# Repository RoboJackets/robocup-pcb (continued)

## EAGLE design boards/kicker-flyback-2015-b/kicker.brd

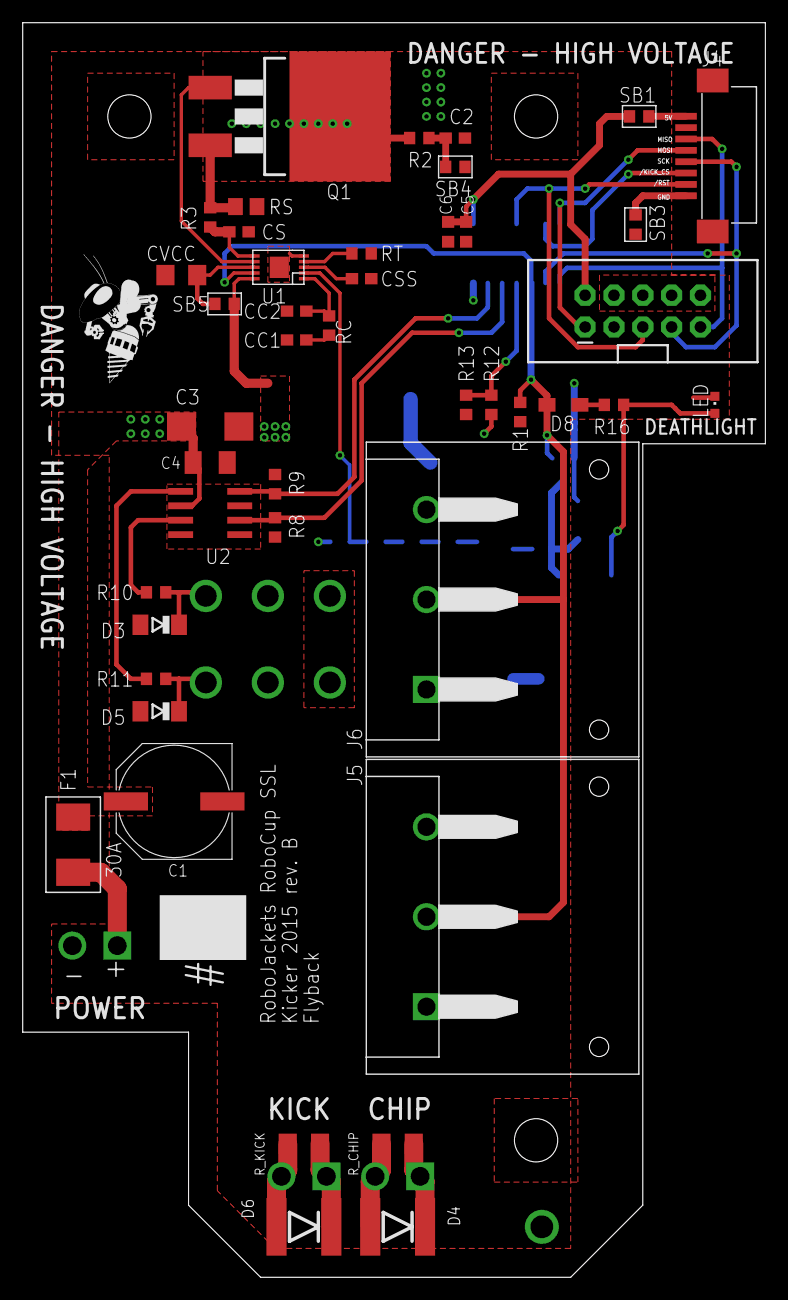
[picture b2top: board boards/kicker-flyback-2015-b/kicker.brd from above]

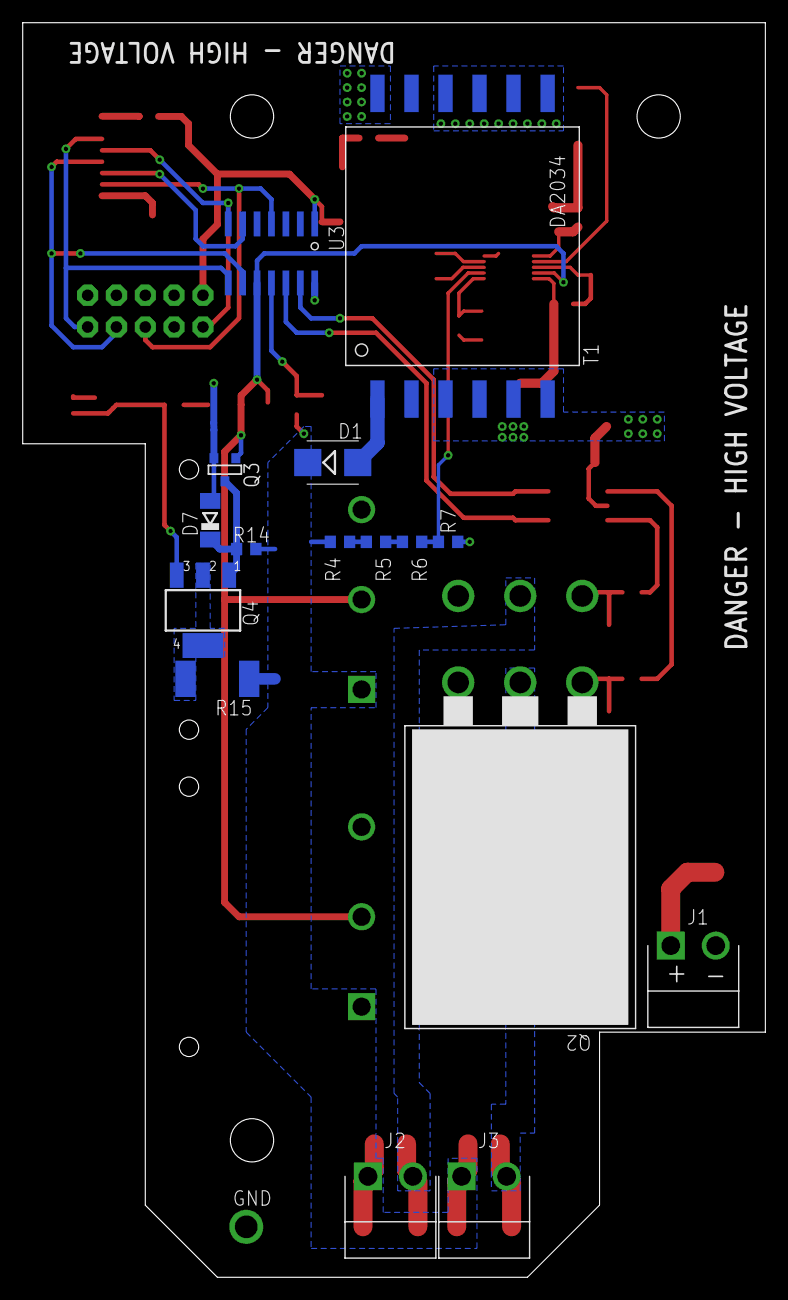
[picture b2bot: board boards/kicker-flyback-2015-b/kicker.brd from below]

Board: 2 copper layers, 65.4 x 110.5 mm, 62 parts (16 on the bottom side), 40 nets.

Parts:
C1: UWT1E471MNL1GS; PANASONIC_G
C2: 220pF 100V; C0603
C3: 47uF; C/6032-28R
C4: 4.7uF; C1206K
C5: 47u; C0603K
C6: 4.7u; C0603K
CC1: 22nF; C0603
CC2: 100pF; C0603
CS: 22nF; C0603
CSS: 100nF; C0603
CVCC: 4.7uF, 25v; C1206
D1: STTH3R06U; SMB
D3, D5, D7: BZV55-B18,115; SOD80C
D4, D6: DO-214AB
D8: BAS16H; SOD323-W
F1: 30A; NANO2_157
J1: POWER; JST_VH_2_RA
J2: CHIP; JST_VH_2_RA
J3: KICK; JST_VH_2_RA
J4: 0528520870
J5, J6: DF22L-3RIGHT_ANGLE; DF22L-3-H
JP1: M05X2SHD_LOCK; 2X5-SHROUDED_LOCK
LED: LTST-S270KRKT; CHIPLED_0603
Q1: STB40NF20; D2PACK
Q2: TO264_2
Q3: FDV303N; SOT-23
Q4: FQT1N80; SOT223
R1, R8, R9: 10.0k; R0603
R2, R3: 22; R0603
R4, R5: 1.00M, 1% (MCR03EZPFX1004); R0603
R6: 470k 1%; R0603
R7: 16.20k, 1% (MCR03EZPFX1622); R0603
R10, R11: 10; R0603
R12: 1.00M 1%; R0603
R13: 16.2k 1%; R0603
R14: 10M; R0603
R15: RHC2512FT33K0; R2512
R16: 220; R0603
RC: 6.8k; R0603
RS: 0.015 (ERJ-6BWFR015V); R0805
RT: 140k; R0603
R_CHIP: NP; R1206
R_KICK: NP; R1206
SB1: 5V_SEL; SB0603
SB3: GND_NC; SB0603
SB4, SB5: NO; SB0603
T1: DA2034
TP1: GND; VIA_2MM
U1: LT3757; MSOP-10-MSE
U2: IX4427N; SOIC-8
U3: ATTINY441/841SSU/SSUR; SOIC-14
U$1: ROBOBUZZ_0.6X

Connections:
5V: J4.8, SB1.1
+12V: C1.+, C3.+, C4.1, F1.P$2, SB5.1, T1.3, T1.4, T1.5, T1.6, U1.10, U2.6
/KICK_CS: J4.3, U3.6
/RST: J4.2, JP1.5, U3.4
CHARGE: D8.A, J5.2, J6.2, Q3.3, R1.2, U1.9, U3.10
CHIP: R8.2, U2.2, U3.12
GND: C1.-, C2.2, C3.-, C4.2, C5.2, C6.2, CC1.2, CC2.2, CS.2, CSS.2, CVCC.2, D3.A, D5.A, D7.A, J1.2, J5.3, J6.3, JP1.4, JP1.6, JP1.8, JP1.10, LED.C, Q2.E_BOT, Q2.E_TOP, Q3.2, R1.1, R7.1, R8.1, R9.1, R13.1, RS.1, RT.2, SB3.1, SB4.2, T1.12, TP1.P$1, U1.5, U1.11, U2.3, U3.14
HV: D1.C, D4.C, D6.C, J2.1, J3.1, J5.1, J6.1, R4.2, R12.2, R14.2, R15.2, R_CHIP.2, R_KICK.2
KICK: R9.2, U2.4, U3.13
MISO: J4.6, JP1.9, U3.8
MOSI: J4.5, JP1.1, U3.7
unnamed: D3.C, Q2.G_TOP, R10.2
unnamed: Q1.1, U1.7
unnamed: J4.1, SB3.2
unnamed: CC2.1, RC.1, U1.1
unnamed: CC1.1, RC.2
unnamed: R11.1, U2.5
unnamed: R4.1, R5.2
unnamed: D5.C, Q2.G_BOT, R11.2
unnamed: R5.1, R6.2
unnamed: D6.A, J3.2, Q2.C_BOT, R_KICK.1
unnamed: D4.A, J2.2, Q2.C_TOP, R_CHIP.1
unnamed: R10.1, U2.7
unnamed: D7.C, Q3.1, Q4.1, R14.1
unnamed: Q4.2, Q4.4, R15.1
unnamed: F1.P$1, J1.1
unnamed: CSS.1, U1.3
unnamed: RT.1, U1.4
unnamed: CVCC.1, SB5.2, U1.8
unnamed: LED.A, Q4.3, R16.2
unnamed: CS.1, R3.1, U1.6
unnamed: C2.1, R2.1, SB4.1
unnamed: D8.C, R16.1
unnamed: Q1.2, R2.2, T1.7, T1.8, T1.9, T1.10
unnamed: D1.A, T1.1
NAG: Q1.3, R3.2, RS.2
SCK: J4.4, JP1.7, U3.9
VDD: C5.1, C6.1, JP1.2, SB1.2, U3.1
VFB: R6.1, R7.2, U1.2
V_MONITOR: R12.1, R13.2, U3.11

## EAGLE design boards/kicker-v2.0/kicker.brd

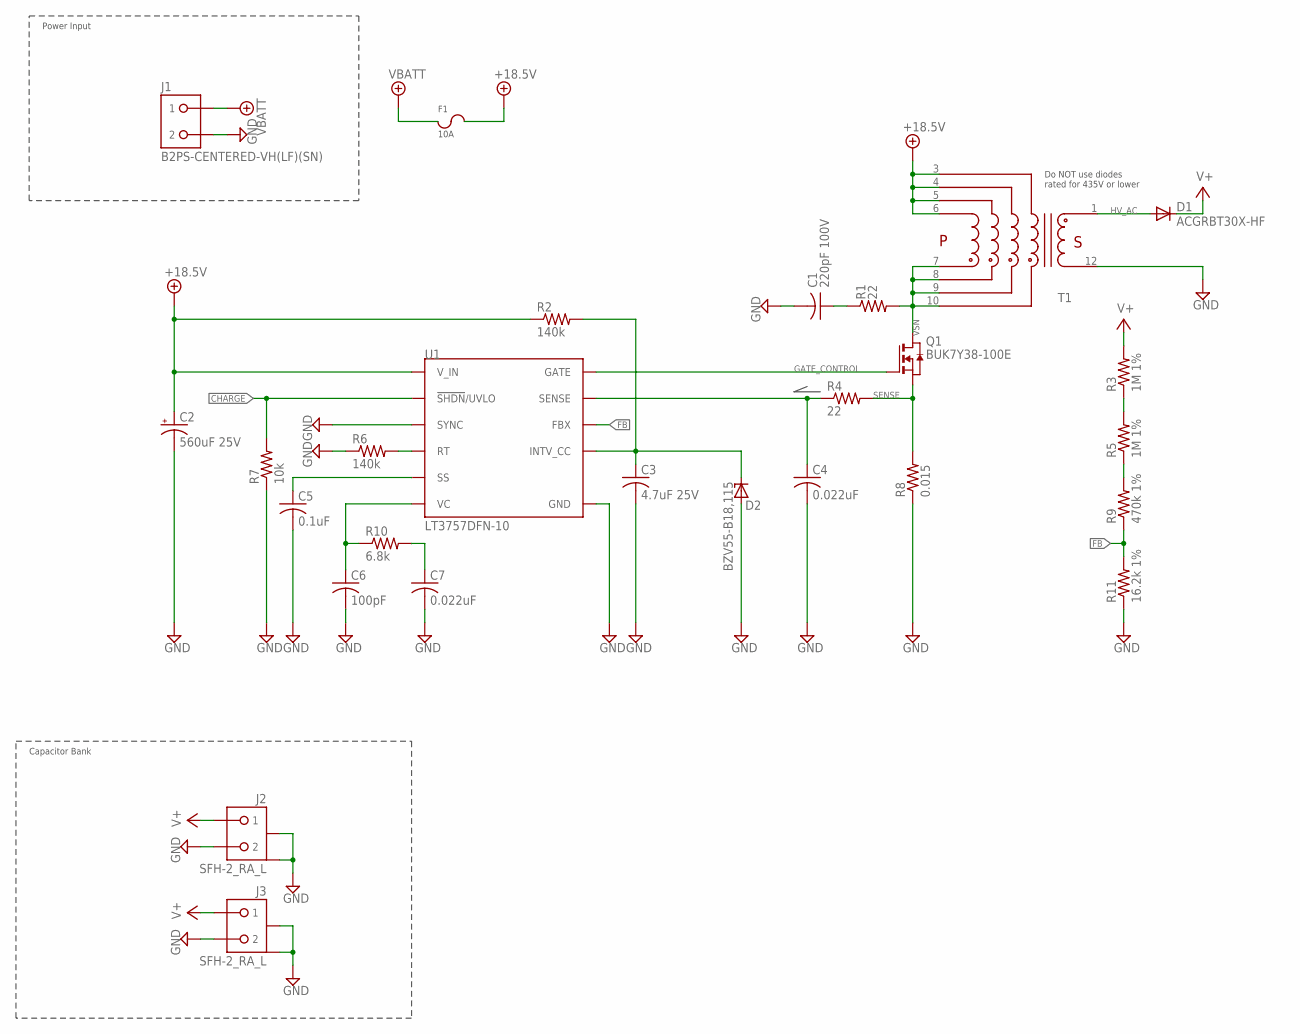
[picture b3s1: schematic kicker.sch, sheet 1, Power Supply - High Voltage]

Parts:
C1: 220pF 100V; C0603
C2: 560uF 25V; UD-10X10_NICHICON
C3: 4.7uF 25V; C0603
C4, C7: 0.022uF; C0603
C5: 0.1uF; C0603
C6: 100pF; C0603
D1: ACGRBT30X-HF; D2114
D2: BZV55-B18,115; SOD80C
F1: 10A; F1812
J1: B2PS-CENTERED-VH(LF)(SN); B2PS-CENTERED
J2, J3: SFH-2_RA_L
Q1: BUK7Y38-100E; LFPAK
R1: 22; R1206
R2, R6: 140k; R0603
R3, R5: 1M 1%; R0603
R4: 22; R0603
R7: 10k; R0603
R8: 0.015; R0603
R9: 470k 1%; R0603
R10: 6.8k; R0603
R11: 16.2k 1%; R0603
T1: DA203X-ALDA2034; DA2034
U1: LT3757DFN-10; DFN-10

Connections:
+18.5V: C2.+, F1.2, R2.1, T1.3, T1.4, T1.5, T1.6, U1.10 (V_IN); also elsewhere on the board
CHARGE: R7.2, U1.9 (!SHDN!/UVLO); also elsewhere on the board
FB: R9.1, R11.2, U1.2 (FBX); also elsewhere on the board
GATE_CONTROL: Q1.4 (G), U1.7 (GATE)
GND: C1.2, C2.-, C3.2, C4.2, C5.2, C6.2, C7.2, D2.A, J1.2, J2.2, J2.LEG1, J2.LEG2, J3.2, J3.LEG1, J3.LEG2, R6.1, R7.1, R8.1, R11.1, T1.12, U1.5 (SYNC), U1.PAD (GND); also elsewhere on the board
HV_AC: D1.A, T1.1
INTVCC: C3.1, D2.C, R2.2, U1.8 (INTV_CC)
unnamed: C7.1, R10.2
unnamed: C6.1, R10.1, U1.1 (VC)
unnamed: C1.1, R1.1
RTIMING: R6.2, U1.4 (RT)
RTOP12: R3.1, R5.2
RTOP23: R5.1, R9.2
SENSE: Q1.1 (S), Q1.2 (S), Q1.3 (S), R4.2, R8.2
SENSE_LPF: C4.1, R4.1, U1.6 (SENSE)
SOFT-START: C5.1, U1.3 (SS)
V+: D1.K (C), J2.1, J3.1, R3.2; also elsewhere on the board
VBATT: F1.1, J1.1; also elsewhere on the board
VSN: Q1.5678 (D), R1.2, T1.7, T1.8, T1.9, T1.10

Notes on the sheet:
Do NOT use diodes rated for 435V or lower
Power Input
Capacitor Bank

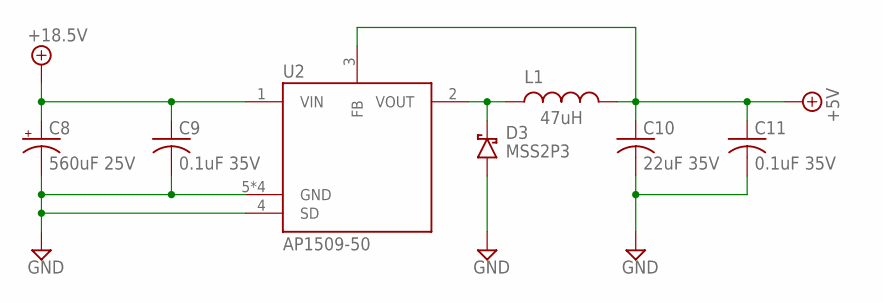
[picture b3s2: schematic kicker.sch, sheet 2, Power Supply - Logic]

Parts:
C8: 560uF 25V; UD-10X10_NICHICON
C9, C11: 0.1uF 35V; C0603
C10: 22uF 35V; C0805
D3: MSS2P3; MICROSMP
L1: 47uH; NR60XX_NRS60XX
U2: AP1509-50; SOIC-8

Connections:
+5V: C10.1, C11.1, L1.1, U2.3 (FB); also elsewhere on the board
+18.5V: C8.+, C9.1, U2.1 (VIN); also elsewhere on the board
GND: C8.-, C9.2, C10.2, C11.2, D3.A, U2.4 (SD), U2.5 (GND), U2.6 (GND), U2.7 (GND), U2.8 (GND); also elsewhere on the board
unnamed: D3.K (C), L1.2, U2.2 (VOUT)

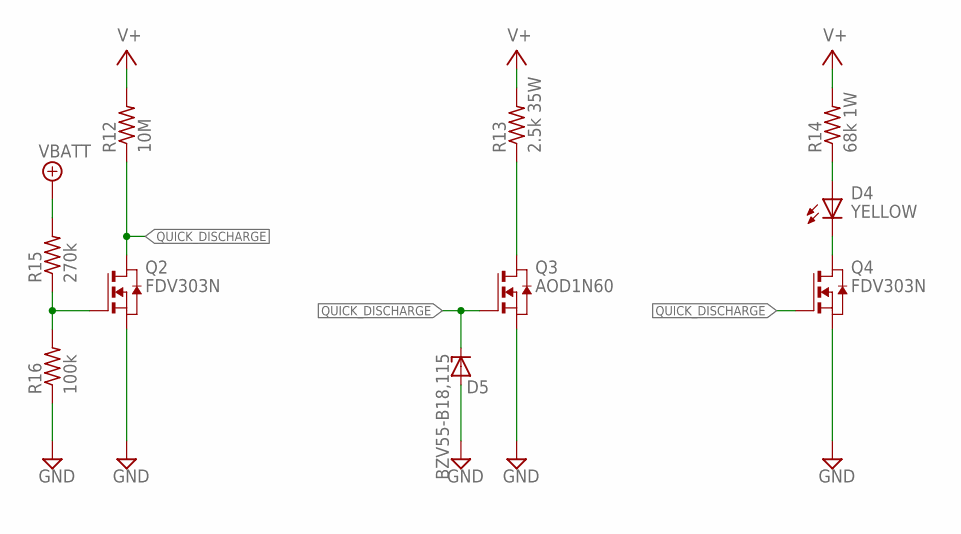
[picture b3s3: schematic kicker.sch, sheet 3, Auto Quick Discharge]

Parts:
D4: YELLOW; CHIP-LED0603
D5: BZV55-B18,115; SOD80C
Q2, Q4: FDV303N; SOT-23-3
Q3: AOD1N60; DPAK
R12: 10M; R0603
R13: 2.5k 35W; DPAK_TDH
R14: 68k 1W; R0612
R15: 270k; R0603
R16: 100k; R0603

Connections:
GND: D5.A, Q2.2 (S), Q3.3 (S), Q4.2 (S), R16.1; also elsewhere on the board
unnamed: Q2.1 (G), R15.1, R16.2
unnamed: D4.C (K), Q4.3 (D)
unnamed: Q3.FIN (D), R13.1 (PIN1)
unnamed: D4.A, R14.1 (PIN1)
QUICK_DISCHARGE: D5.C, Q2.3 (D), Q3.1 (G), Q4.1 (G), R12.1
V+: R12.2, R13.2 (PIN2), R14.2 (PIN2); also elsewhere on the board
VBATT: R15.2; also elsewhere on the board

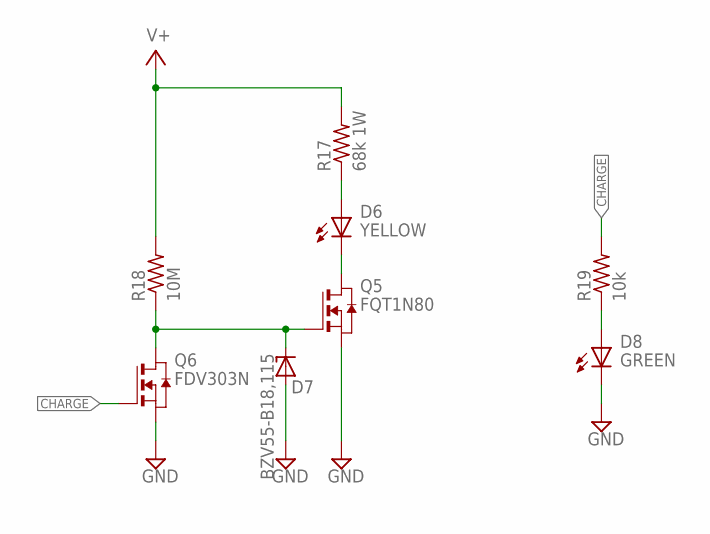
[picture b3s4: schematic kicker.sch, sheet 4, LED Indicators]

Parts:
D6: YELLOW; CHIP-LED0603
D7: BZV55-B18,115; SOD80C
D8: GREEN; CHIP-LED0603
Q5: FQT1N80; SOT223
Q6: FDV303N; SOT-23-3
R17: 68k 1W; R0612
R18: 10M; R0603
R19: 10k; R0603

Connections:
CHARGE: Q6.1 (G), R19.2; also elsewhere on the board
GND: D7.A, D8.C (K), Q5.3 (S), Q6.2 (S); also elsewhere on the board
unnamed: D6.A, R17.1 (PIN1)
unnamed: D6.C (K), Q5.2 (D), Q5.4 (D)
unnamed: D8.A, R19.1
unnamed: D7.C, Q5.1 (G), Q6.3 (D), R18.1
V+: R17.2 (PIN2), R18.2; also elsewhere on the board

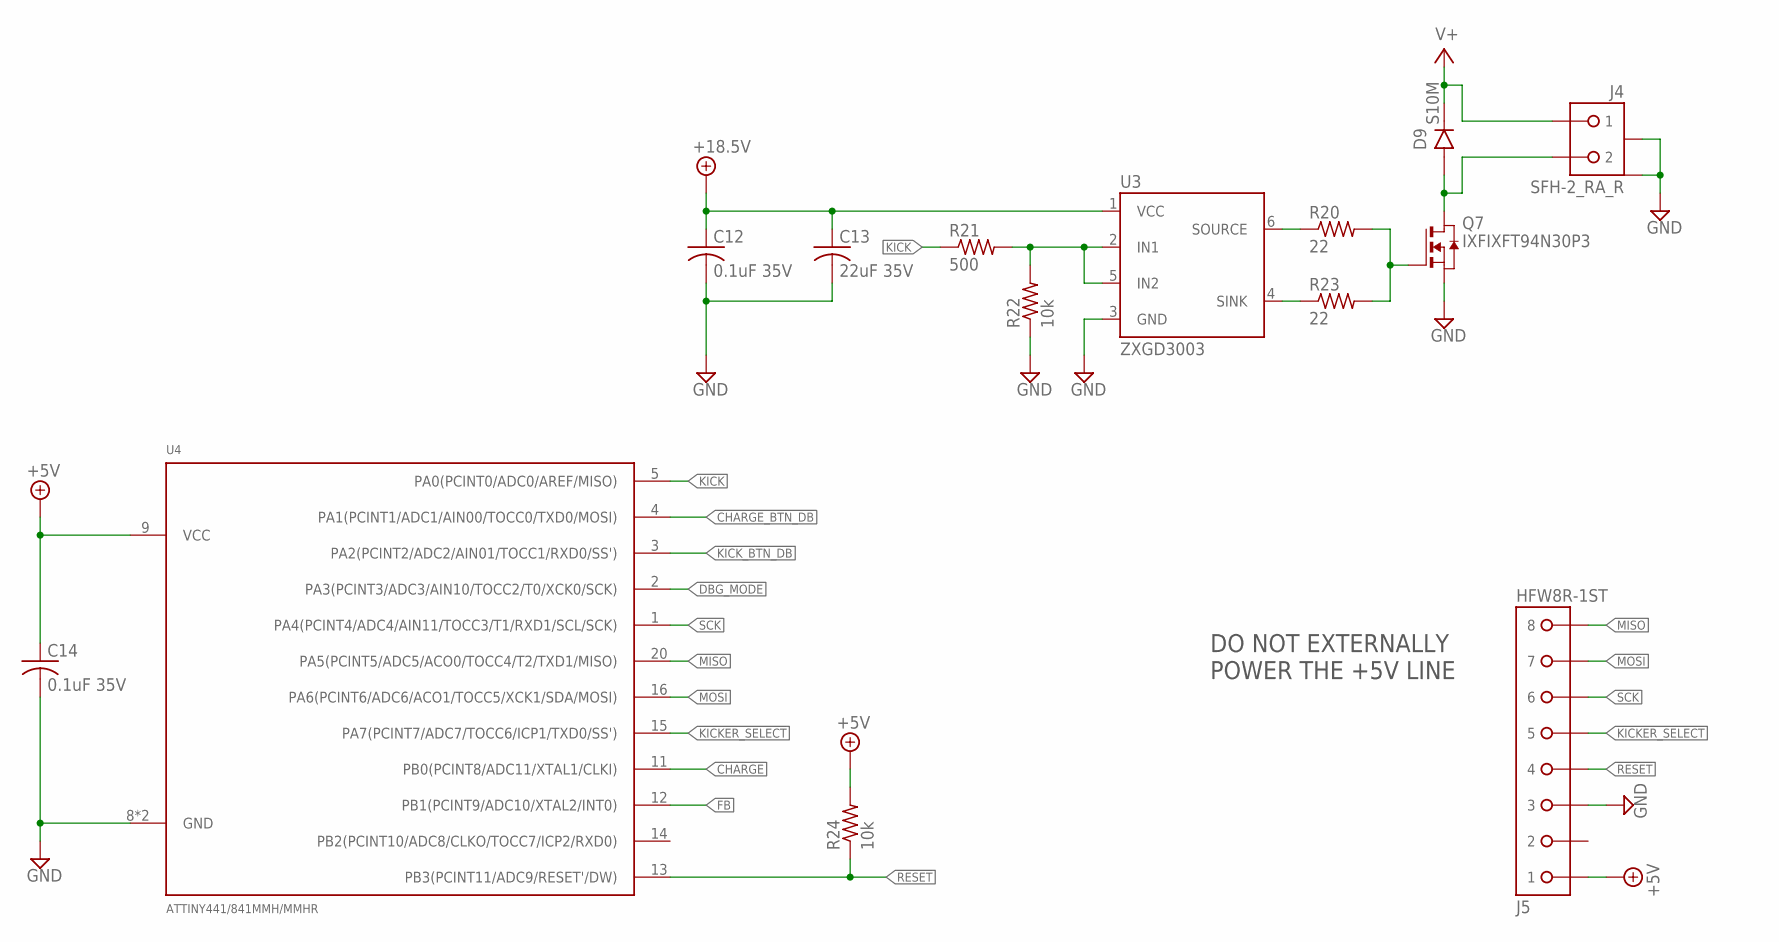
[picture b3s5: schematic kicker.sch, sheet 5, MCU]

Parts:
C12, C14: 0.1uF 35V; C0603
C13: 22uF 35V; C0805
D9: S10M; DO-214AB
J4: SFH-2_RA_R
J5: HFW8R-1ST
Q7: IXFIXFT94N30P3; TO-268
R20, R23: 22; R1206
R21: 500; R0603
R22, R24: 10k; R0603
U3: ZXGD3003; SOT-23-6
U4: ATTINY441/841MMH/MMHR; VQFN-20_3X3MM

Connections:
!CHARGE_BTN_DB: U4.4 (PA1(PCINT1/ADC1/AIN00/TOCC0/TXD0/MOSI)); also elsewhere on the board
!KICKER_SELECT: J5.5, U4.15 (PA7(PCINT7/ADC7/TOCC6/ICP1/TXD0/SS'))
!KICK_BTN_DB: U4.3 (PA2(PCINT2/ADC2/AIN01/TOCC1/RXD0/SS')); also elsewhere on the board
!RESET: J5.4, R24.1, U4.13 (PB3(PCINT11/ADC9/RESET'/DW))
+5V: C14.1, J5.1, R24.2, U4.9 (VCC); also elsewhere on the board
+18.5V: C12.1, C13.1, U3.1 (VCC); also elsewhere on the board
CHARGE: U4.11 (PB0(PCINT8/ADC11/XTAL1/CLKI)); also elsewhere on the board
DBG_MODE: U4.2 (PA3(PCINT3/ADC3/AIN10/TOCC2/T0/XCK0/SCK)); also elsewhere on the board
FB: U4.12 (PB1(PCINT9/ADC10/XTAL2/INT0)); also elsewhere on the board
GND: C12.2, C13.2, C14.2, J4.LEG1, J4.LEG2, J5.3, Q7.3 (S), R22.1, U3.3 (GND), U4.8 (GND), U4.PAD (GND); also elsewhere on the board
KICK: R21.1, U4.5 (PA0(PCINT0/ADC0/AREF/MISO))
KICKER: D9.A, J4.2, Q7.4 (D)
MISO: J5.8, U4.20 (PA5(PCINT5/ADC5/ACO0/TOCC4/T2/TXD1/MISO))
MOSI: J5.7, U4.16 (PA6(PCINT6/ADC6/ACO1/TOCC5/XCK1/SDA/MOS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)
unnamed: R21.2, R22.2, U3.2 (IN1), U3.5 (IN2)
unnamed: Q7.1 (G), R20.2, R23.2
unnamed: R20.1, U3.6 (SOURCE)
unnamed: R23.1, U3.4 (SINK)
SCK: J5.6, U4.1 (PA4(PCINT4/ADC4/AIN11/TOCC3/T1/RXD1/SCL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)
V+: D9.C, J4.1; also elsewhere on the board

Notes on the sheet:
DO NOT EXTERNALLY POWER THE +5V LINE

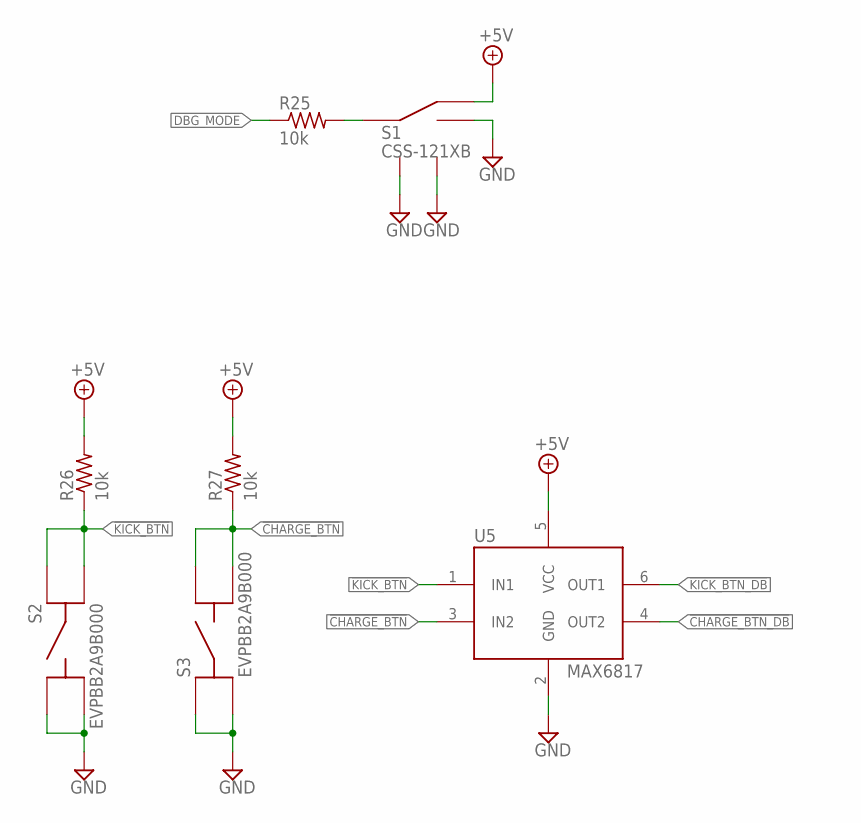
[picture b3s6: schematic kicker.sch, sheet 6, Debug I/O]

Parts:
R25, R26, R27: 10k; R0603
S1: CSS-121XB
S2, S3: EVPBB2A9B000
U5: MAX6817; SOT-23-6

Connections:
!CHARGE_BTN: R27.1, S3.B1, S3.B2, U5.3 (IN2)
!CHARGE_BTN_DB: U5.4 (OUT2); also elsewhere on the board
!KICK_BTN: R26.1, S2.A1, S2.A2, U5.1 (IN1)
!KICK_BTN_DB: U5.6 (OUT1); also elsewhere on the board
+5V: R26.2, R27.2, S1.1 (A), U5.5 (VCC); also elsewhere on the board
DBG_MODE: R25.1; also elsewhere on the board
GND: S1.2 (B), S1.LEG1, S1.LEG4 (LEG2), S2.B1, S2.B2, S3.A1, S3.A2, U5.2 (GND); also elsewhere on the board
unnamed: R25.2, S1.3 (COMMON)

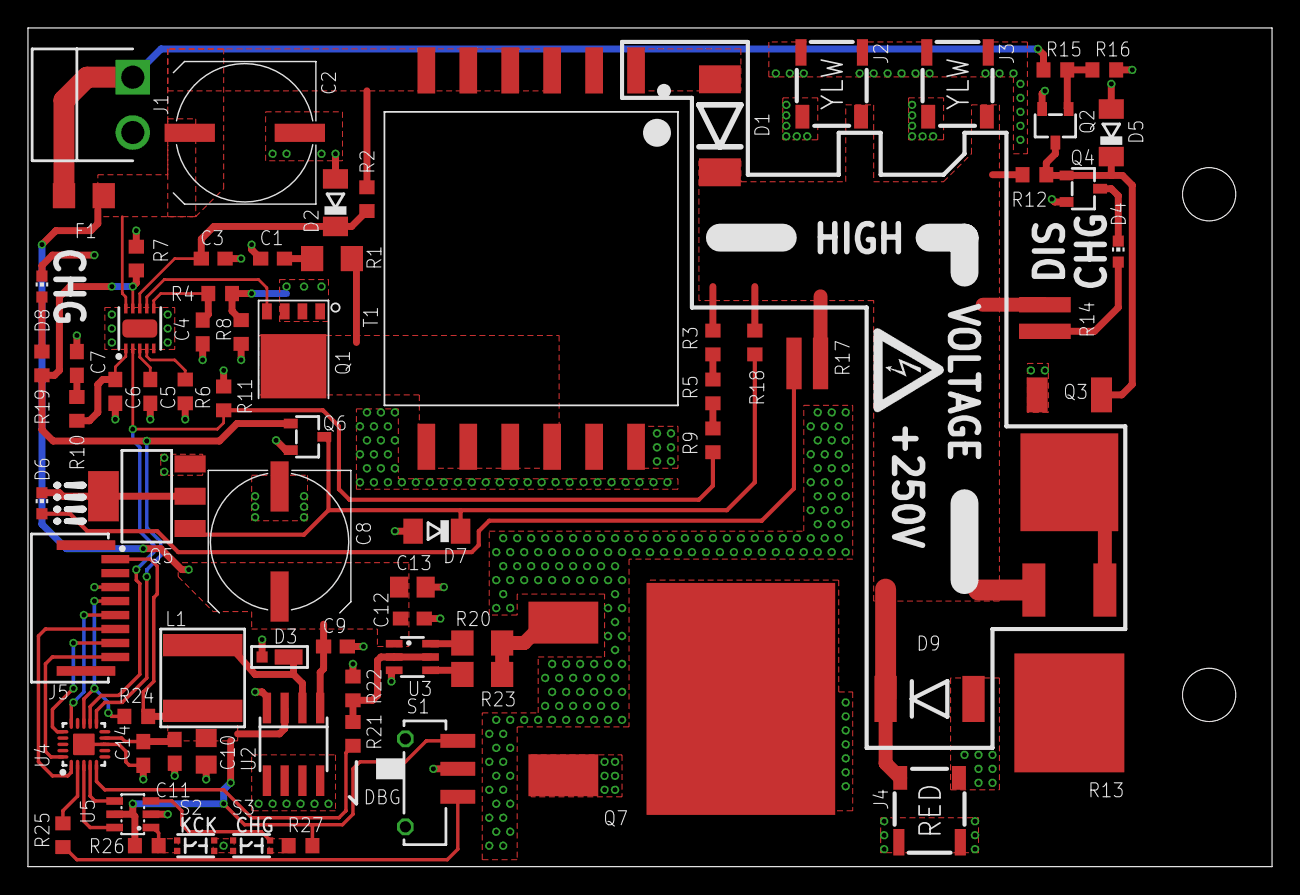
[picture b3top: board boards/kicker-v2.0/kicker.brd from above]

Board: 2 copper layers, 89.0 x 60.0 mm, 74 parts (0 on the bottom side), 47 nets.

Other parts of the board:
U$1: HV_WARNING

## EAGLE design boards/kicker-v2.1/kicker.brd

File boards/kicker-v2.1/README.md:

# Kicker Board

Board containing circuitry to charge capacitors then discharge into solenoid(s).

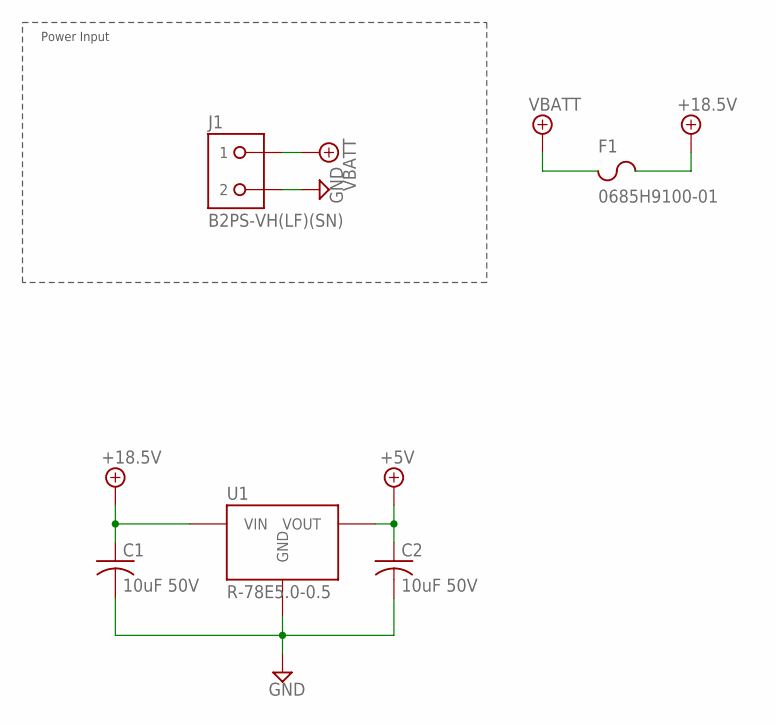
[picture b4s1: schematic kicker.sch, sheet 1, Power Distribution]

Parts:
C1, C2: 10uF 50V; C0603
F1: 0685H9100-01; F1206
J1: B2PS-VH(LF)(SN); B2PS-CENTERED
U1: R-78E5.0-0.5; R-78E

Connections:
+5V: C2.1, U1.3 (VOUT); also elsewhere on the board
+18.5V: C1.1, F1.2, U1.1 (VIN); also elsewhere on the board
GND: C1.2, C2.2, J1.2, U1.2 (GND); also elsewhere on the board
VBATT: F1.1, J1.1

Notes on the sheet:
Power Input

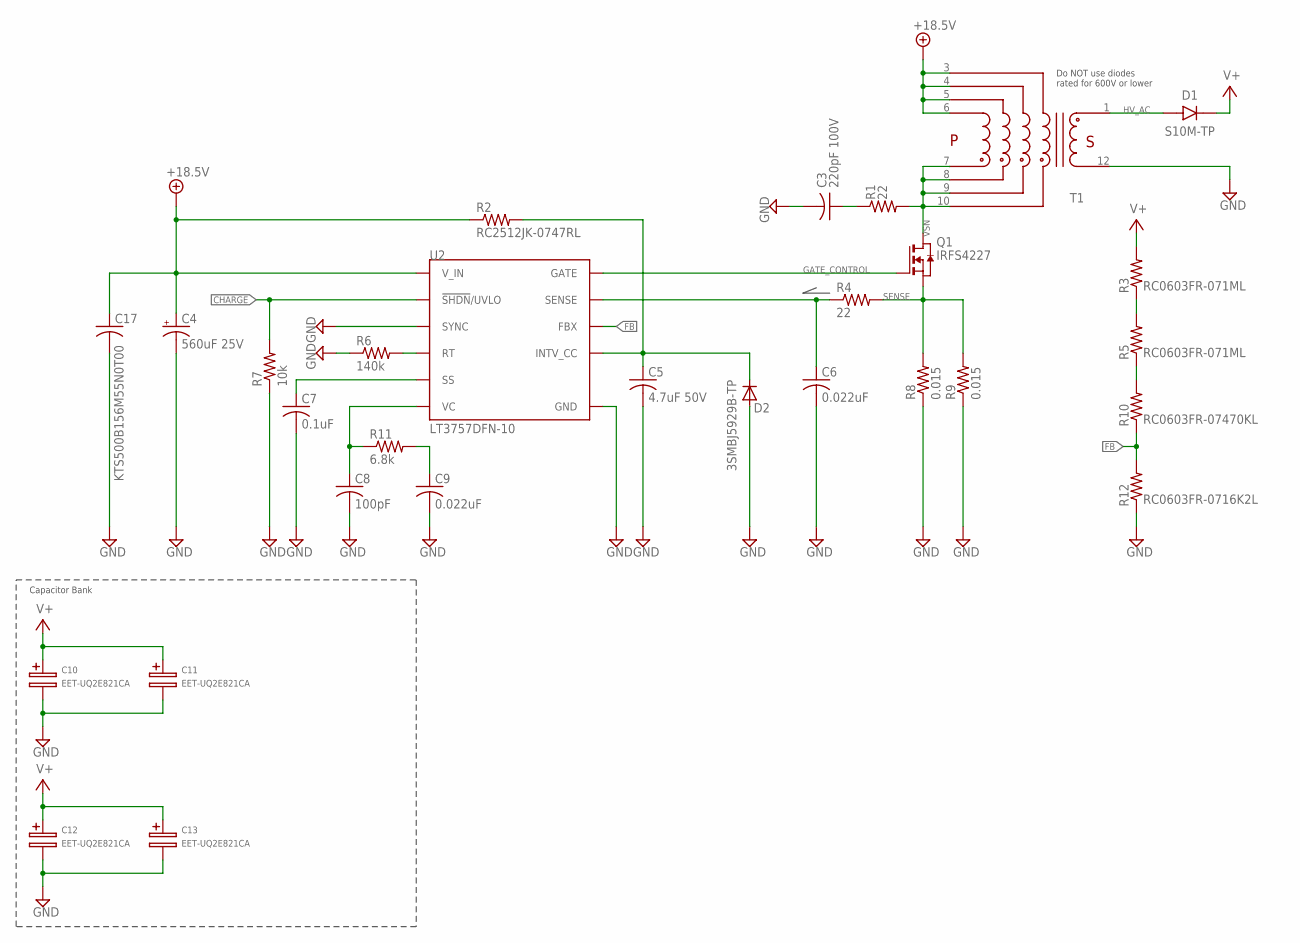
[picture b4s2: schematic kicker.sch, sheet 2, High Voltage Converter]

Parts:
C3: 220pF 100V; C0603
C4: 560uF 25V; UD-10X10_NICHICON
C5: 4.7uF 50V; C0603
C6, C9: 0.022uF; C0603
C7: 0.1uF; C0603
C8: 100pF; C0603
C10, C11: EET-UQ2E821CA; 25MM-DIA_40MM-HGT_HORIZ
C12, C13: EET-UQ2E821CA; 25MM-DIA_40MM-HGT_HORIZ_MIRRORED
C17: KTS500B156M55N0T00; C2220K
D1: S10M-TP; DO-214AB
D2: 3SMBJ5929B-TP; DO214AA
Q1: IRFS4227; D2PAK
R1, R4: 22; R0805
R2: RC2512JK-0747RL; R2512
R3, R5: RC0603FR-071ML; R0603
R6: 140k; R0603
R7: 10k; R0603
R8, R9: 0.015; R1206
R10: RC0603FR-07470KL; R0603
R11: 6.8k; R0603
R12: RC0603FR-0716K2L; R0603
T1: DA203X-ALDA2034; DA2034
U2: LT3757DFN-10; DFN-10

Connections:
+18.5V: C4.+, C17.1, R2.1, T1.3, T1.4, T1.5, T1.6, U2.10 (V_IN); also elsewhere on the board
CHARGE: R7.2, U2.9 (!SHDN!/UVLO); also elsewhere on the board
FB: R10.1, R12.2, U2.2 (FBX)
GATE_CONTROL: Q1.1 (G), U2.7 (GATE)
GND: C3.2, C4.-, C5.2, C6.2, C7.2, C8.2, C9.2, C10.-, C11.-, C12.-, C13.-, C17.2, D2.A, R6.1, R7.1, R8.1, R9.1, R12.1, T1.12, U2.5 (SYNC), U2.PAD (GND); also elsewhere on the board
HV_AC: D1.A, T1.1
INTVCC: C5.1, D2.C, R2.2, U2.8 (INTV_CC)
unnamed: C9.1, R11.2
unnamed: C3.1, R1.1
RTIMING: R6.2, U2.4 (RT)
RTOP12: R3.1, R5.2
RTOP23: R5.1, R10.2
SENSE: Q1.3 (S), R4.2, R8.2, R9.2
SENSE_LPF: C6.1, R4.1, U2.6 (SENSE)
SOFT-START: C7.1, U2.3 (SS)
V+: C10.+, C11.+, C12.+, C13.+, D1.C, R3.2; also elsewhere on the board
VC: C8.1, R11.1, U2.1 (VC)
VSN: Q1.2 (D), R1.2, T1.7, T1.8, T1.9, T1.10

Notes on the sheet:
Do NOT use diodes rated for 600V or lower
Capacitor Bank

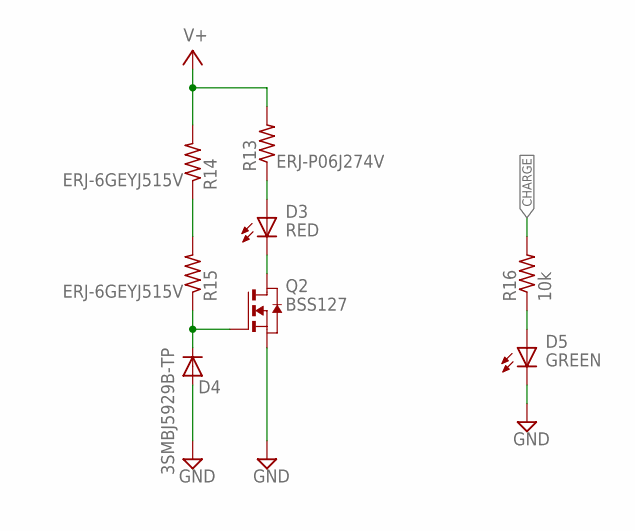
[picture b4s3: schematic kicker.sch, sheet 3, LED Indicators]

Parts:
D3: RED; CHIP-LED0603
D4: 3SMBJ5929B-TP; DO214AA
D5: GREEN; CHIP-LED0603
Q2: BSS127; SOT-23-3
R13: ERJ-P06J274V; R0805
R14, R15: ERJ-6GEYJ515V; R0805
R16: 10k; R0603

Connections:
CHARGE: R16.2; also elsewhere on the board
GND: D4.A, D5.C (K), Q2.2 (S); also elsewhere on the board
unnamed: D3.A, R13.1
unnamed: D3.C (K), Q2.3 (D)
unnamed: D5.A, R16.1
unnamed: R14.1, R15.2
unnamed: D4.C, Q2.1 (G), R15.1
V+: R13.2, R14.2; also elsewhere on the board

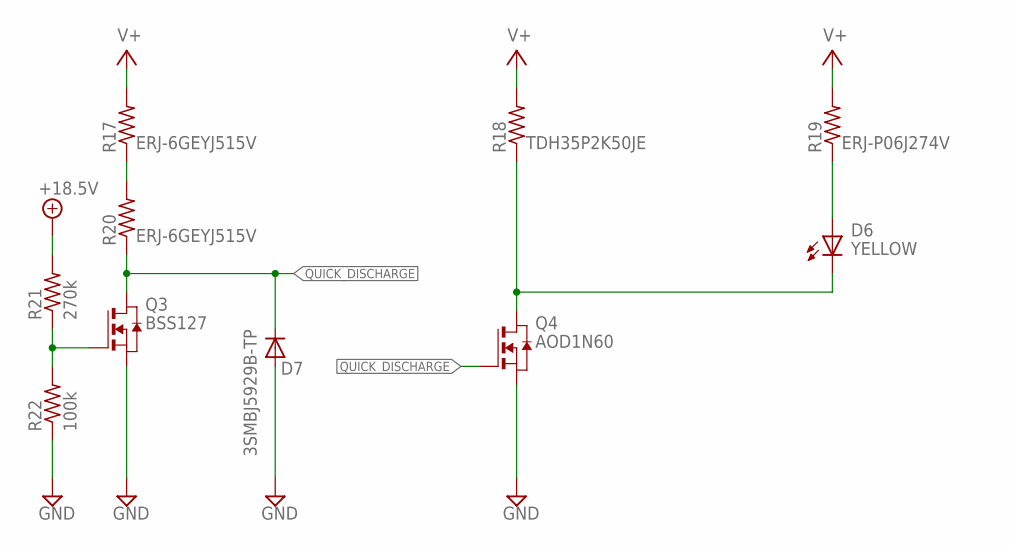
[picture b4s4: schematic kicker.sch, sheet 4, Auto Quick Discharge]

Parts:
D6: YELLOW; CHIP-LED0603
D7: 3SMBJ5929B-TP; DO214AA
Q3: BSS127; SOT-23-3
Q4: AOD1N60; DPAK
R17, R20: ERJ-6GEYJ515V; R0805
R18: TDH35P2K50JE; DPAK_TDH
R19: ERJ-P06J274V; R0805
R21: 270k; R0603
R22: 100k; R0603

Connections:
+18.5V: R21.2; also elsewhere on the board
GND: D7.A, Q3.2 (S), Q4.3 (S), R22.1; also elsewhere on the board
unnamed: R17.1, R20.2
unnamed: Q3.1 (G), R21.1, R22.2
unnamed: D6.C (K), Q4.FIN (D), R18.1 (PIN1)
unnamed: D6.A, R19.1
QUICK_DISCHARGE: D7.C, Q3.3 (D), Q4.1 (G), R20.1
V+: R17.2, R18.2 (PIN2), R19.2; also elsewhere on the board

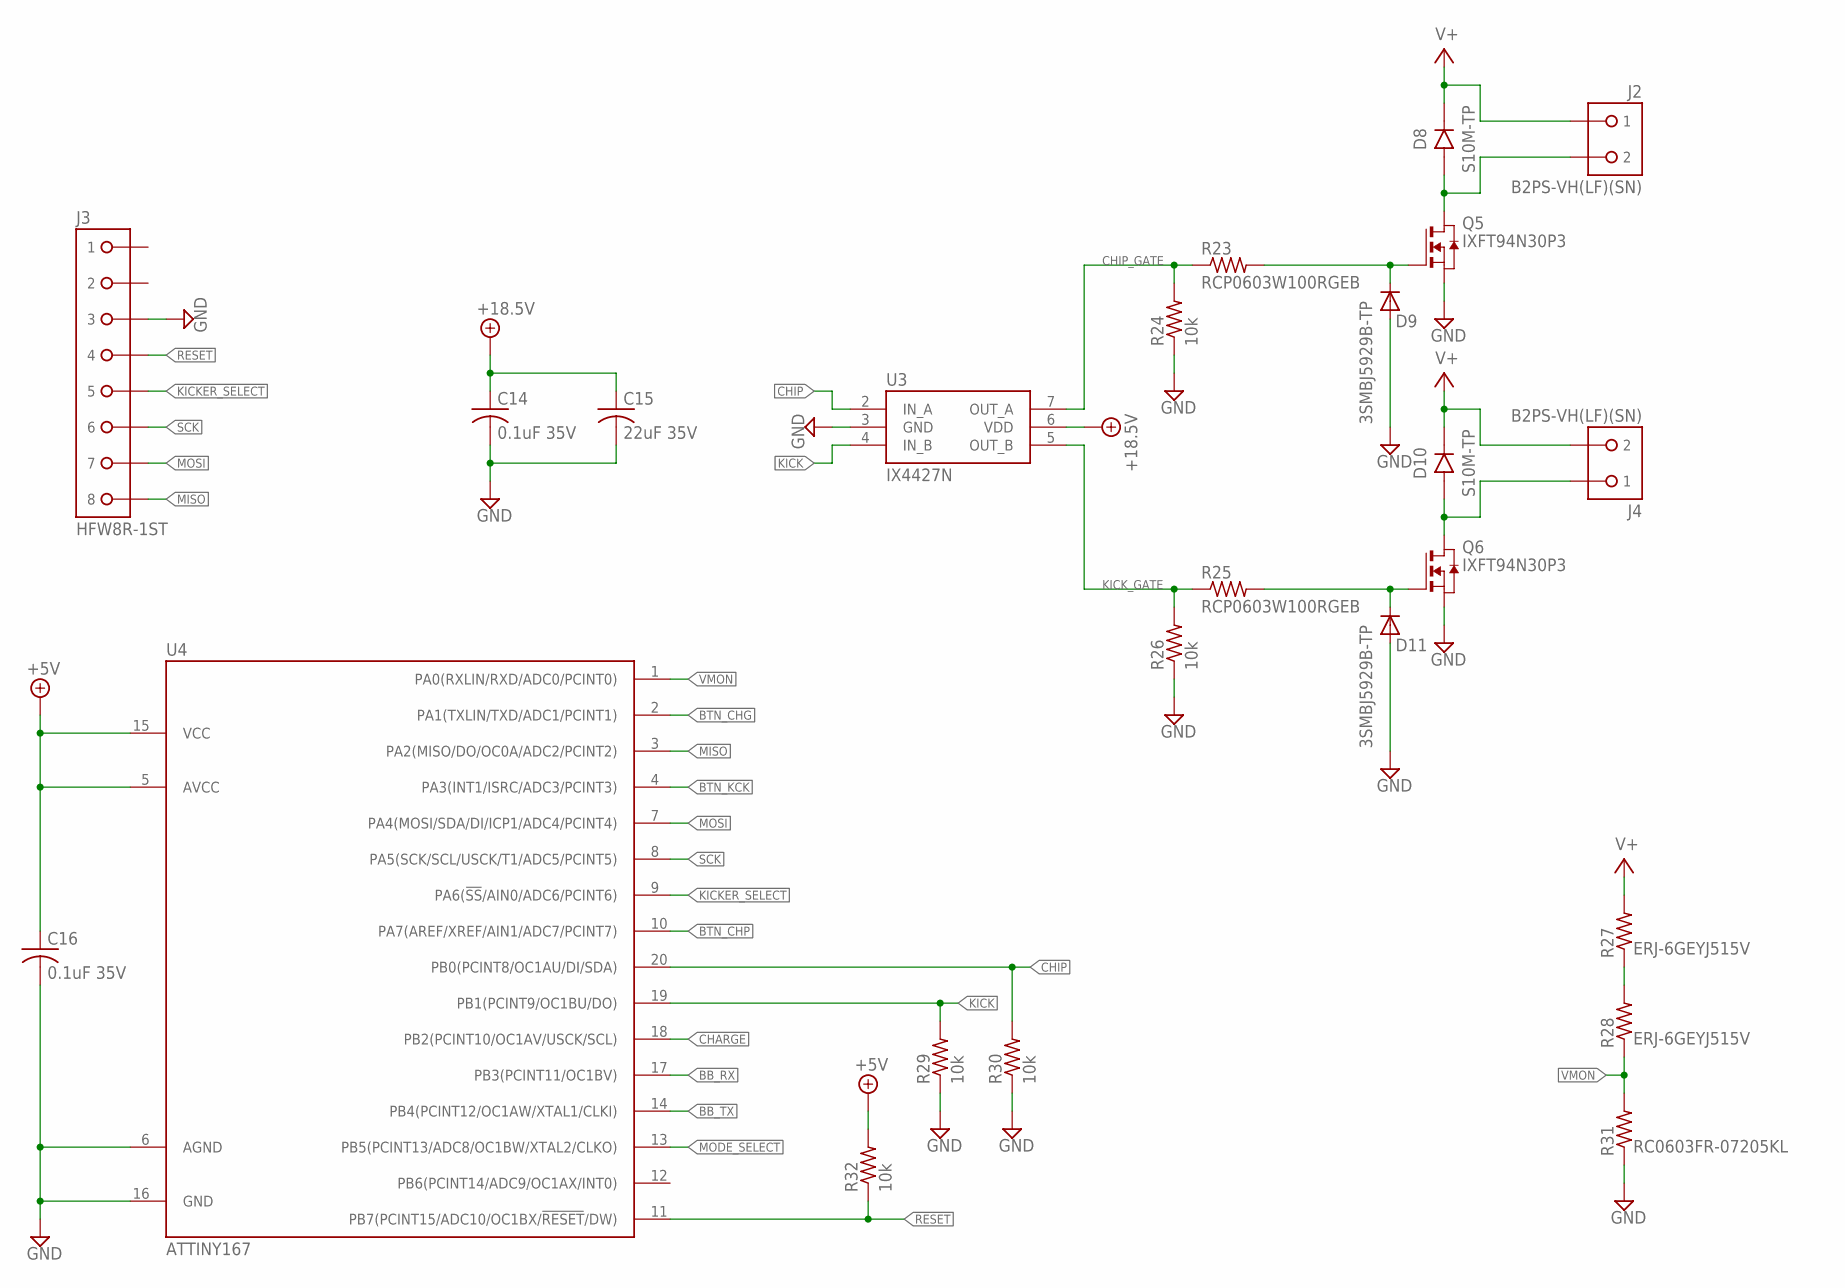
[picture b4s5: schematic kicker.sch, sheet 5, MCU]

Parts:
C14, C16: 0.1uF 35V; C0603
C15: 22uF 35V; C0805
D8, D10: S10M-TP; DO-214AB
D9, D11: 3SMBJ5929B-TP; DO214AA
J2, J4: B2PS-VH(LF)(SN); B2PS-CENTERED
J3: HFW8R-1ST
Q5, Q6: IXFT94N30P3; TO-268
R23, R25: RCP0603W100RGEB; R0603W
R24, R26, R29, R30, R32: 10k; R0603
R27, R28: ERJ-6GEYJ515V; R0805
R31: RC0603FR-07205KL; R0603
U3: IX4427N; SOIC-8
U4: ATTINY167; SOIC-20

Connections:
!BTN_CHG: U4.2 (PA1(TXLIN/TXD/ADC1/PCINT1)); also elsewhere on the board
!BTN_CHP: U4.10 (PA7(AREF/XREF/AIN1/ADC7/PCINT7)); also elsewhere on the board
!BTN_KCK: U4.4 (PA3(INT1/ISRC/ADC3/PCINT3)); also elsewhere on the board
!KICKER_SELECT: J3.5, U4.9 (PA6(!SS!/AIN0/ADC6/PCINT6))
!RESET: J3.4, R32.1, U4.11 (PB7(PCINT15/ADC10/OC1BX/!RESET!/DW))
+5V: C16.1, R32.2, U4.5 (AVCC), U4.15 (VCC); also elsewhere on the board
+18.5V: C14.1, C15.1, U3.6 (VDD); also elsewhere on the board
BB_RX: U4.17 (PB3(PCINT11/OC1BV)); also elsewhere on the board
BB_TX: U4.14 (PB4(PCINT12/OC1AW/XTAL1/CLKI)); also elsewhere on the board
CHARGE: U4.18 (PB2(PCINT10/OC1AV/USCK/SCL)); also elsewhere on the board
CHIP: R30.2, U3.2 (IN_A), U4.20 (PB0(PCINT8/OC1AU/DI/SDA))
CHIPPER: D8.A, J2.2, Q5.4 (D)
CHIP_GATE: R23.1 (PIN1), R24.2, U3.7 (OUT_A)
GND: C14.2, C15.2, C16.2, D9.A, D11.A, J3.3, Q5.3 (S), Q6.3 (S), R24.1, R26.1, R29.1, R30.1, R31.1, U3.3 (GND), U4.6 (AGND), U4.16 (GND); also elsewhere on the board
KICK: R29.2, U3.4 (IN_B), U4.19 (PB1(PCINT9/OC1BU/DO))
KICKER: D10.A, J4.1, Q6.4 (D)
KICK_GATE: R25.1 (PIN1), R26.2, U3.5 (OUT_B)
MISO: J3.8, U4.3 (PA2(MISO/DO/OC0A/ADC2/PCINT2))
MODE_SELECT: U4.13 (PB5(PCINT13/ADC8/OC1BW/XTAL2/CLKO)); also elsewhere on the board
MOSI: J3.7, U4.7 (PA4(MOSI/SDA/DI/ICP1/ADC4/PCINT4))
unnamed: D9.C, Q5.1 (G), R23.2 (PIN2)
unnamed: D11.C, Q6.1 (G), R25.2 (PIN2)
unnamed: R27.1, R28.2
SCK: J3.6, U4.8 (PA5(SCK/SCL/USCK/T1/ADC5/PCINT5))
V+: D8.C, D10.C, J2.1, J4.2, R27.2; also elsewhere on the board
VMON: R28.1, R31.2, U4.1 (PA0(RXLIN/RXD/ADC0/PCINT0))

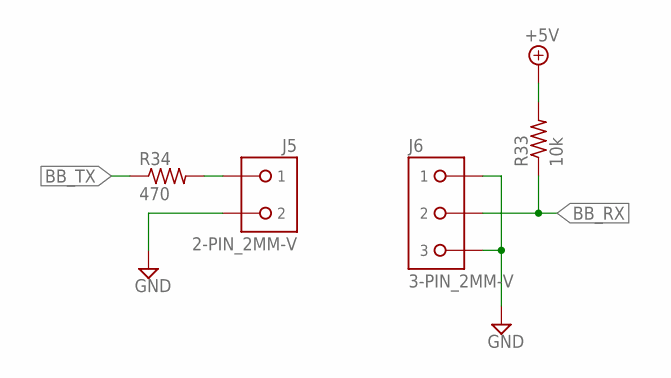
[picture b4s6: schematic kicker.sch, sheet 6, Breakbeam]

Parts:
J5: 2-PIN_2MM-V; 2MM-2-V
J6: 3-PIN_2MM-V; 2MM-3-V
R33: 10k; R0603
R34: 470; R0603

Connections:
+5V: R33.2; also elsewhere on the board
BB_RX: J6.2, R33.1; also elsewhere on the board
BB_TX: R34.1; also elsewhere on the board
GND: J5.2, J6.1, J6.3; also elsewhere on the board
unnamed: J5.1, R34.2

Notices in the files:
parts and their libraries:
SparkFun-Connectors: Licensing: Creative Commons ShareAlike 4.0 International - https://creativecommons.org/licenses/by-sa/4.0
